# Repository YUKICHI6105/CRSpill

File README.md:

# CRSpill  
第一回大改造～ブランチはPCBAで大半の部品をつけられるようにしました。発注するときはこちらをご利用ください。

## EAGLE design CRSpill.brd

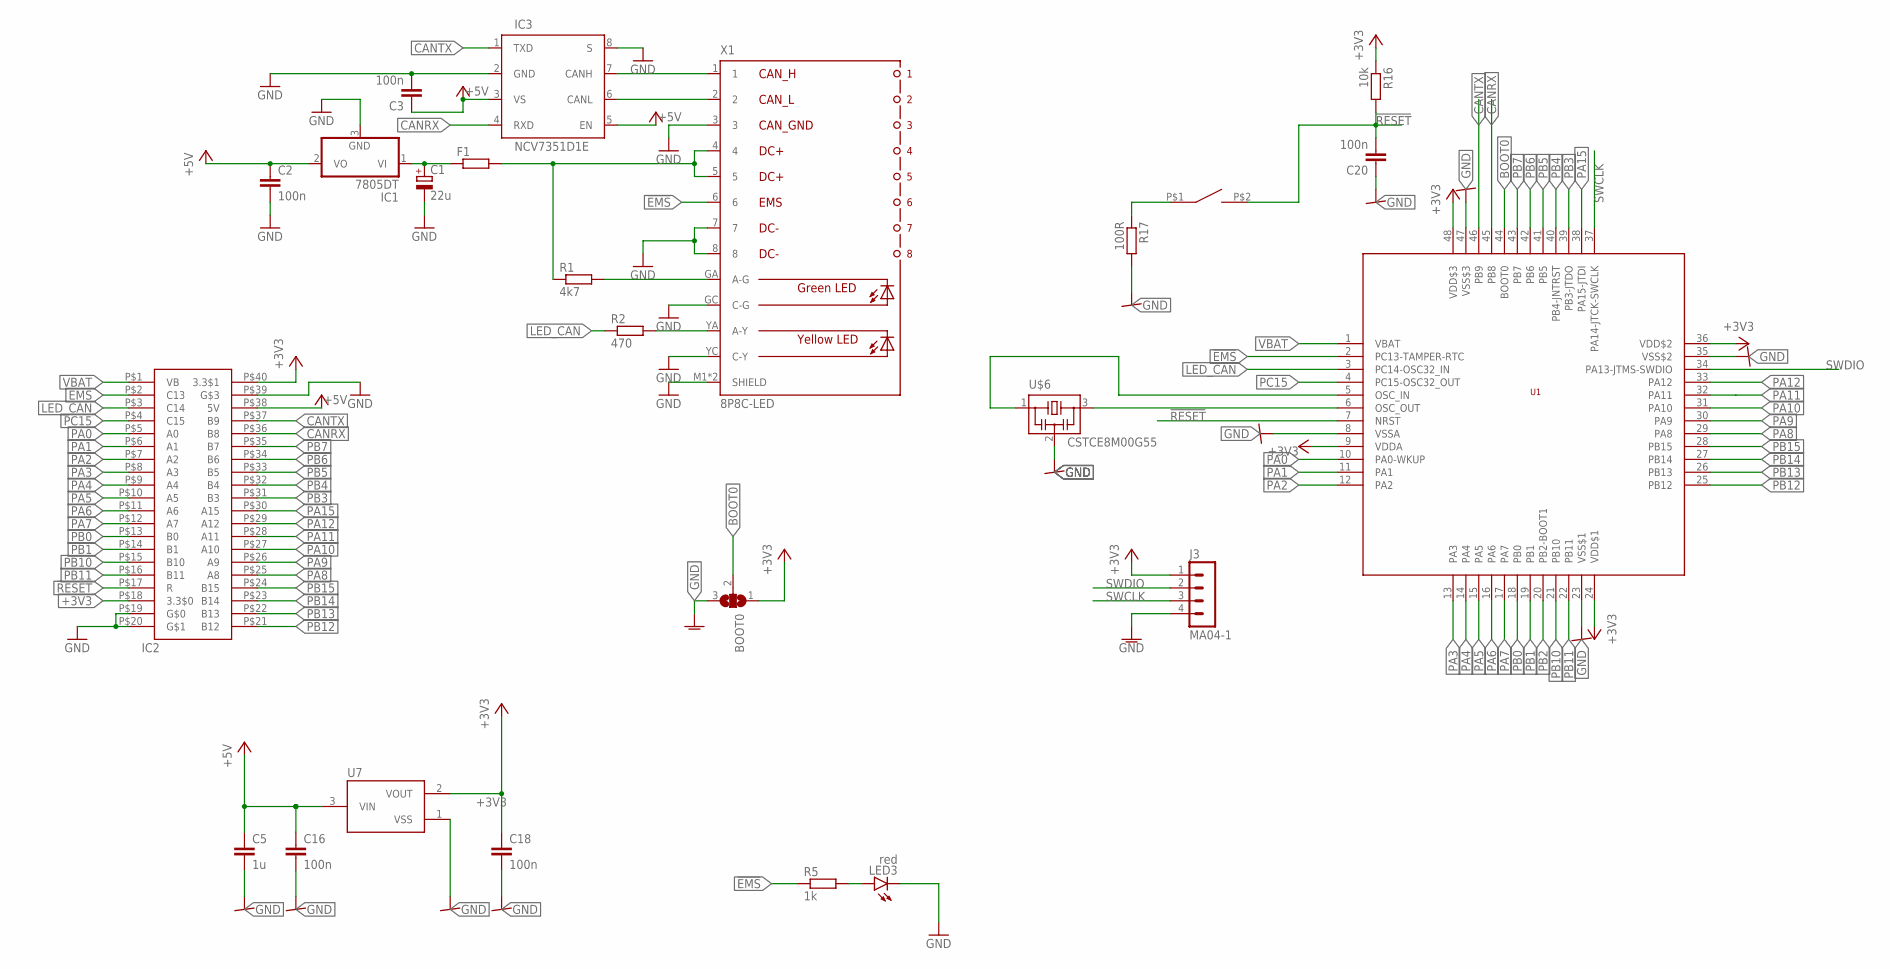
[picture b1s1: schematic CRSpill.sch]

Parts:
BOOT0: SJ2W; SJ_2
C1: 22u; E2,5-5
C2, C3, C16, C18, C20: 100n; C0603
C5: 1u; C0603
F1: R-EU_R1206; R1206
IC1: 7805DT; TO252
IC2: BLUE_PILL
IC3: NCV7351D1E; SO08
J3: MA04-1
LED3: red; CHIPLED_0805
R1: 4k7; R0603
R2: 470; R0603
R5: 1k; R0603
R16: 10k; R0603
R17: 100R; R0603
SW1: SWITCH_TACTILETOP; SWITCH_TACTILE_3X6
U1: STM32F103C8; LQFP48
U7: XC6206; SOT95P240X110-3
U$6: CSTCE8M00G55
X1: 8P8C-LED

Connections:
!EMS: IC2.P$2 (C13), R5.1, U1.2 (PC13-TAMPER-RTC), X1.6
!RESET: C20.2, IC2.P$17 (R), R16.2, SW1.P$2 (2), U1.7 (NRST)
+3V3: BOOT0.1, C18.1, IC2.P$18 (3.3$0), IC2.P$40 (3.3$1), J3.1, R16.1, U1.9 (VDDA), U1.24 (VDD$1), U1.36 (VDD$2), U1.48 (VDD$3), U7.2 (VOUT)
+5V: C2.1, C3.1, C5.1, C16.1, IC1.2 (VO), IC2.P$38 (5V), IC3.3 (VS), IC3.5 (EN), U7.3 (VIN); also elsewhere on the board
BOOT0: BOOT0.2, U1.44 (BOOT0)
CANRX: IC2.P$36 (B8), IC3.4 (RXD), U1.45 (PB8)
CANTX: IC2.P$37 (B9), IC3.1 (TXD), U1.46 (PB9)
GND: BOOT0.3, C1.-, C2.2, C3.2, C5.2, C16.2, C18.2, C20.1, IC1.3 (GND), IC2.P$19, IC2.P$20, IC2.P$39, IC3.2 (GND), IC3.8 (S), J3.4, LED3.C, R17.2, U1.8 (VSSA), U1.23 (VSS$1), U1.35 (VSS$2), U1.47 (VSS$3), U7.1 (VSS), U$6.2, X1.3, X1.7, X1.8, X1.GC (C-G), X1.M1 (SHIELD), X1.M2 (SHIELD), X1.YC (C-Y); also elsewhere on the board
LED_CAN: IC2.P$3 (C14), R2.1, U1.3 (PC14-OSC32_IN)
unnamed: R1.2, X1.GA (A-G)
unnamed: F1.2, R1.1, X1.4, X1.5
unnamed: C1.+, F1.1, IC1.1 (VI)
unnamed: IC3.7 (CANH), X1.1
unnamed: IC3.6 (CANL), X1.2
unnamed: R2.2, X1.YA (A-Y)
unnamed: U1.6 (OSC_OUT), U$6.3
unnamed: LED3.A, R5.2
unnamed: R17.1, SW1.P$1 (1)
unnamed: U1.5 (OSC_IN), U$6.1
PA0: IC2.P$5 (A0), U1.10 (PA0-WKUP)
PA1: IC2.P$6 (A1), U1.11 (PA1)
PA2: IC2.P$7 (A2), U1.12 (PA2)
PA3: IC2.P$8 (A3), U1.13 (PA3)
PA4: IC2.P$9 (A4), U1.14 (PA4)
PA5: IC2.P$10 (A5), U1.15 (PA5)
PA6: IC2.P$11 (A6), U1.16 (PA6)
PA7: IC2.P$12 (A7), U1.17 (PA7)
PA8: IC2.P$25 (A8), U1.29 (PA8)
PA9: IC2.P$26 (A9), U1.30 (PA9)
PA10: IC2.P$27 (A10), U1.31 (PA10)
PA11: IC2.P$28 (A11), U1.32 (PA11)
PA12: IC2.P$29 (A12), U1.33 (PA12)
PA15: IC2.P$30 (A15), U1.38 (PA15-JTDI)
PB0: IC2.P$13 (B0), U1.18 (PB0)
PB1: IC2.P$14 (B1), U1.19 (PB1)
PB2: U1.20 (PB2-BOOT1)
PB3: IC2.P$31 (B3), U1.39 (PB3-JTDO)
PB4: IC2.P$32 (B4), U1.40 (PB4-JNTRST)
PB5: IC2.P$33 (B5), U1.41 (PB5)
PB6: IC2.P$34 (B6), U1.42 (PB6)
PB7: IC2.P$35 (B7), U1.43 (PB7)
PB10: IC2.P$15 (B10), U1.21 (PB10)
PB11: IC2.P$16 (B11), U1.22 (PB11)
PB12: IC2.P$21 (B12), U1.25 (PB12)
PB13: IC2.P$22 (B13), U1.26 (PB13)
PB14: IC2.P$23 (B14), U1.27 (PB14)
PB15: IC2.P$24 (B15), U1.28 (PB15)
PC15: IC2.P$4 (C15), U1.4 (PC15-OSC32_OUT)
SWCLK: J3.3, U1.37 (PA14-JTCK-SWCLK)
SWDIO: J3.2, U1.34 (PA13-JTMS-SWDIO)
VBAT: IC2.P$1 (VB), U1.1 (VBAT)

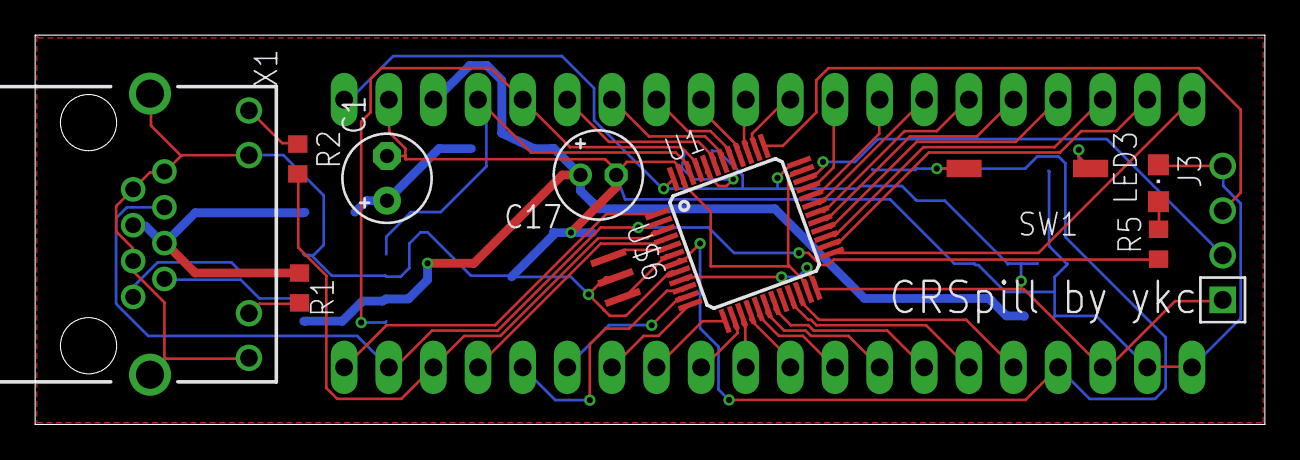
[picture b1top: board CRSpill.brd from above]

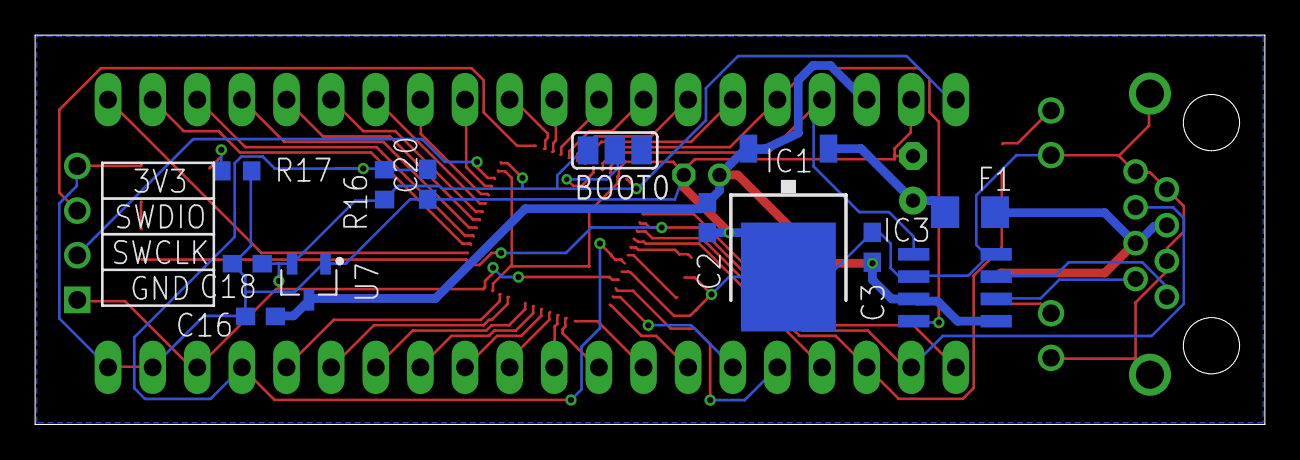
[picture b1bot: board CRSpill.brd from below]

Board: 2 copper layers, 70.0 x 22.2 mm, 24 parts (12 on the bottom side), 50 nets.

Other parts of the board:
C17: 22u; E2-5

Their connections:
+5V: C17.+; also elsewhere on the board
GND: C17.-; also elsewhere on the board

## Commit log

2023-04-15 5V12Vの配線を強化
2023-04-15 未接続部を処理
2023-04-15 size調整
2023-04-17 水晶他諸々修正済み
2023-04-17 boot0他
2023-05-01 ガバーファイル追加
2023-05-09 debug repair
2023-05-09 ガバーファイル削除
2023-05-09 電解コンデンサ1個表面実装用に変更
2023-05-09 bomの修正
2023-05-23 改造完了
2023-05-23 fainal fixed
2023-05-23 100nF add to 3V3
2023-08-13 シルクの追加
